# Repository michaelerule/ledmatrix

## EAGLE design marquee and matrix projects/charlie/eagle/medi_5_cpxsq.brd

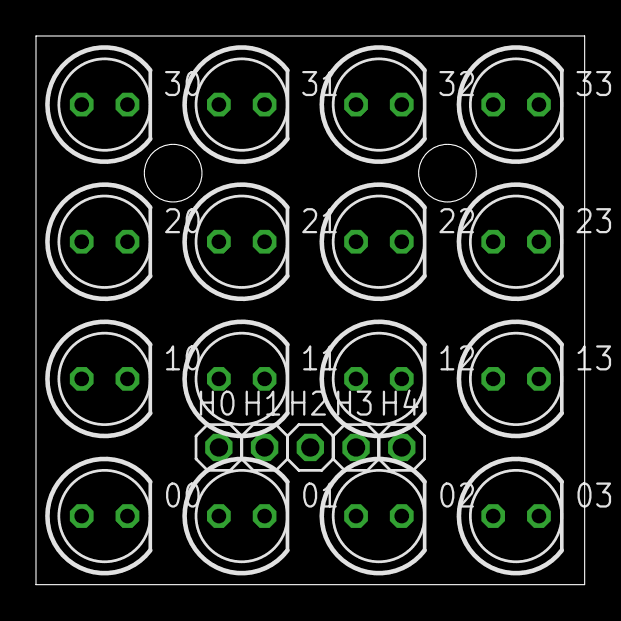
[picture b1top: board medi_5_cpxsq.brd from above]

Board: 2 copper layers, 30.5 x 30.5 mm, 21 parts (0 on the bottom side), 5 nets, no tracks yet.

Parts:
00, 01, 02, 03, 10, 11, 12, 13, 20, 21, 22, 23, 30, 31, 32, 33: LED5MM
H0, H1, H2, H3, H4: 1X01

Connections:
D: 00.A, 11.A, 22.A, 33.A, H4.1
S0: 00.K, 01.A, 02.A, 03.A, 10.K, 20.K, 30.K, H0.1
S1: 01.K, 10.A, 11.K, 12.A, 13.A, 21.K, 31.K, H1.1
S2: 02.K, 12.K, 20.A, 21.A, 22.K, 23.A, 32.K, H2.1
S3: 03.K, 13.K, 23.K, 30.A, 31.A, 32.A, 33.K, H3.1

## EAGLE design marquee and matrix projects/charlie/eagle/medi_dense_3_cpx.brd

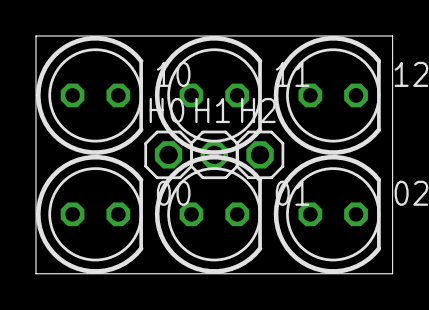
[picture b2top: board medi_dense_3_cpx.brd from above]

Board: 2 copper layers, 19.8 x 13.2 mm, 9 parts (0 on the bottom side), 3 nets, no tracks yet.

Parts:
00, 01, 02, 10, 11, 12: LED5MM
H0, H1, H2: 1X01

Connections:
D: 00.A, 02.K, 11.A, 12.K, H2.1
S0: 00.K, 01.A, 02.A, 10.K, H0.1
S1: 01.K, 10.A, 11.K, 12.A, H1.1

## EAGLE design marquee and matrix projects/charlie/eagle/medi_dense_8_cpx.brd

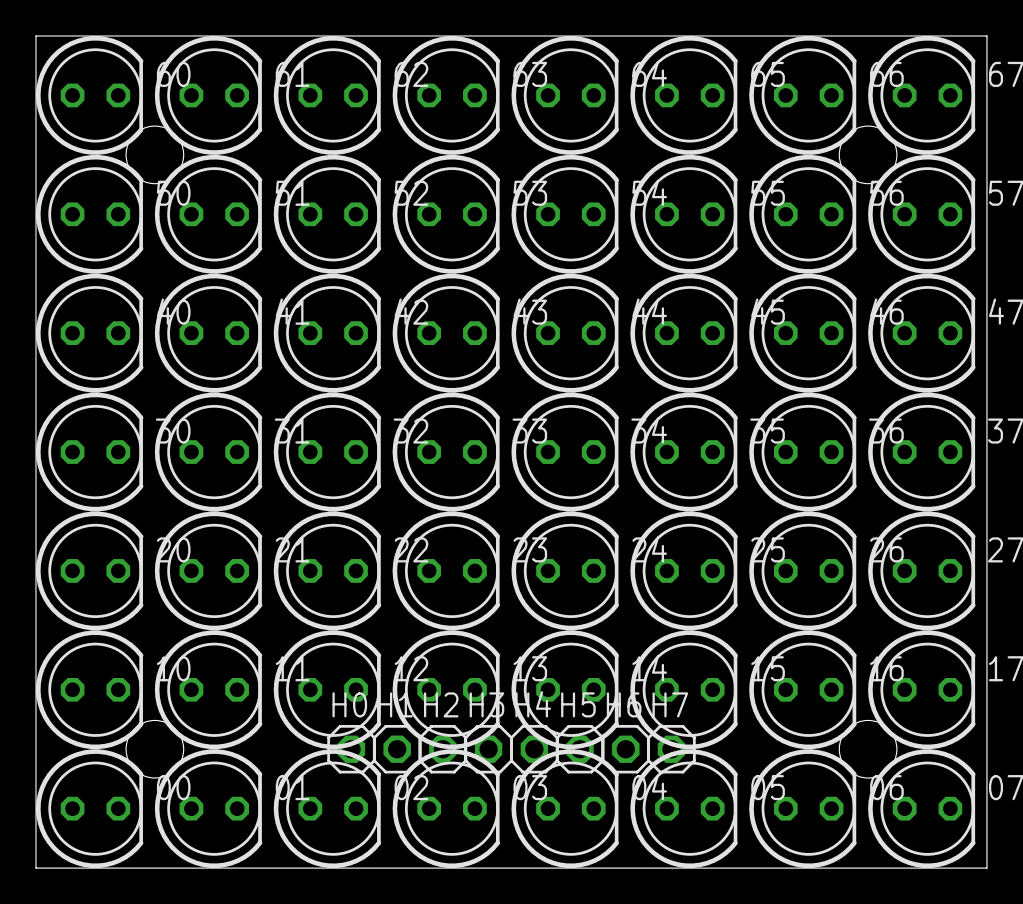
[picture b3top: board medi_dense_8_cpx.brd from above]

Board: 2 copper layers, 52.8 x 46.2 mm, 64 parts (0 on the bottom side), 8 nets, no tracks yet.

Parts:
00, 01, 02, 03, 04, 05, 06, 07, 10, 11, 12, 13, 14, 15, 16, 17, 20, 21, 22, 23, 24, 25, 26, 27, 30, 31, 32, 33, 34, 35, 36, 37, 40, 41, 42, 43, 44, 45, 46, 47, 50, 51, 52, 53, 54, 55, 56, 57, 60, 61, 62, 63, 64, 65, 66, 67: LED5MM
H0, H1, H2, H3, H4, H5, H6, H7: 1X01

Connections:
D: 00.A, 07.K, 11.A, 17.K, 22.A, 27.K, 33.A, 37.K, 44.A, 47.K, 55.A, 57.K, 66.A, 67.K, H7.1
S0: 00.K, 01.A, 02.A, 03.A, 04.A, 05.A, 06.A, 07.A, 10.K, 20.K, 30.K, 40.K, 50.K, 60.K, H0.1
S1: 01.K, 10.A, 11.K, 12.A, 13.A, 14.A, 15.A, 16.A, 17.A, 21.K, 31.K, 41.K, 51.K, 61.K, H1.1
S2: 02.K, 12.K, 20.A, 21.A, 22.K, 23.A, 24.A, 25.A, 26.A, 27.A, 32.K, 42.K, 52.K, 62.K, H2.1
S3: 03.K, 13.K, 23.K, 30.A, 31.A, 32.A, 33.K, 34.A, 35.A, 36.A, 37.A, 43.K, 53.K, 63.K, H3.1
S4: 04.K, 14.K, 24.K, 34.K, 40.A, 41.A, 42.A, 43.A, 44.K, 45.A, 46.A, 47.A, 54.K, 64.K, H4.1
S5: 05.K, 15.K, 25.K, 35.K, 45.K, 50.A, 51.A, 52.A, 53.A, 54.A, 55.K, 56.A, 57.A, 65.K, H5.1
S6: 06.K, 16.K, 26.K, 36.K, 46.K, 56.K, 60.A, 61.A, 62.A, 63.A, 64.A, 65.A, 66.K, 67.A, H6.1

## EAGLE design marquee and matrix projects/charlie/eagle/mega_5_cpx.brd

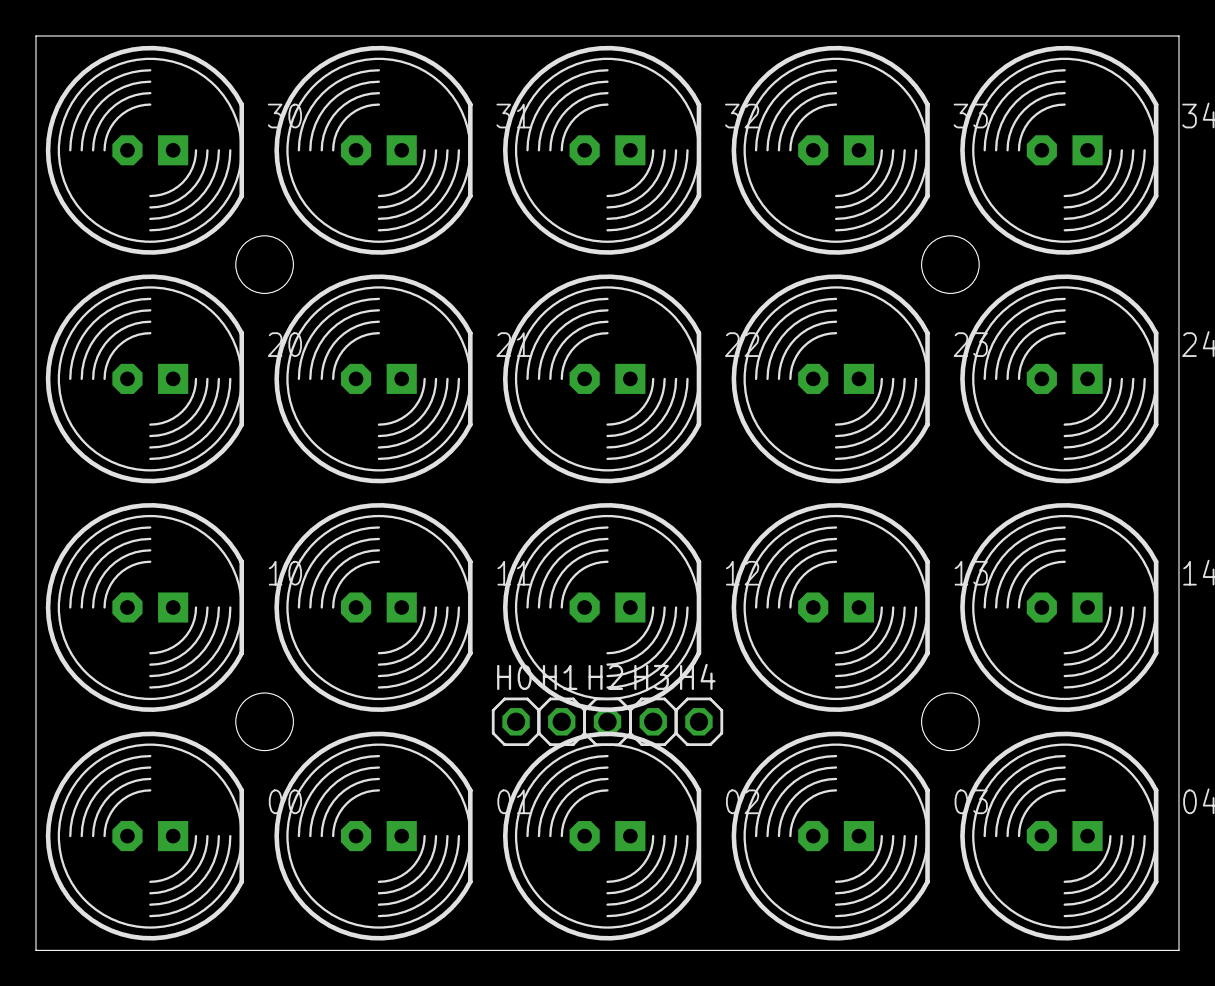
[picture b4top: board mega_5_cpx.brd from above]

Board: 2 copper layers, 63.5 x 50.8 mm, 25 parts (0 on the bottom side), 5 nets, no tracks yet.

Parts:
00, 01, 02, 03, 04, 10, 11, 12, 13, 14, 20, 21, 22, 23, 24, 30, 31, 32, 33, 34: LED10MM
H0, H1, H2, H3, H4: 1X01

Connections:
D: 00.A, 04.K, 11.A, 14.K, 22.A, 24.K, 33.A, 34.K, H4.1
S0: 00.K, 01.A, 02.A, 03.A, 04.A, 10.K, 20.K, 30.K, H0.1
S1: 01.K, 10.A, 11.K, 12.A, 13.A, 14.A, 21.K, 31.K, H1.1
S2: 02.K, 12.K, 20.A, 21.A, 22.K, 23.A, 24.A, 32.K, H2.1
S3: 03.K, 13.K, 23.K, 30.A, 31.A, 32.A, 33.K, 34.A, H3.1

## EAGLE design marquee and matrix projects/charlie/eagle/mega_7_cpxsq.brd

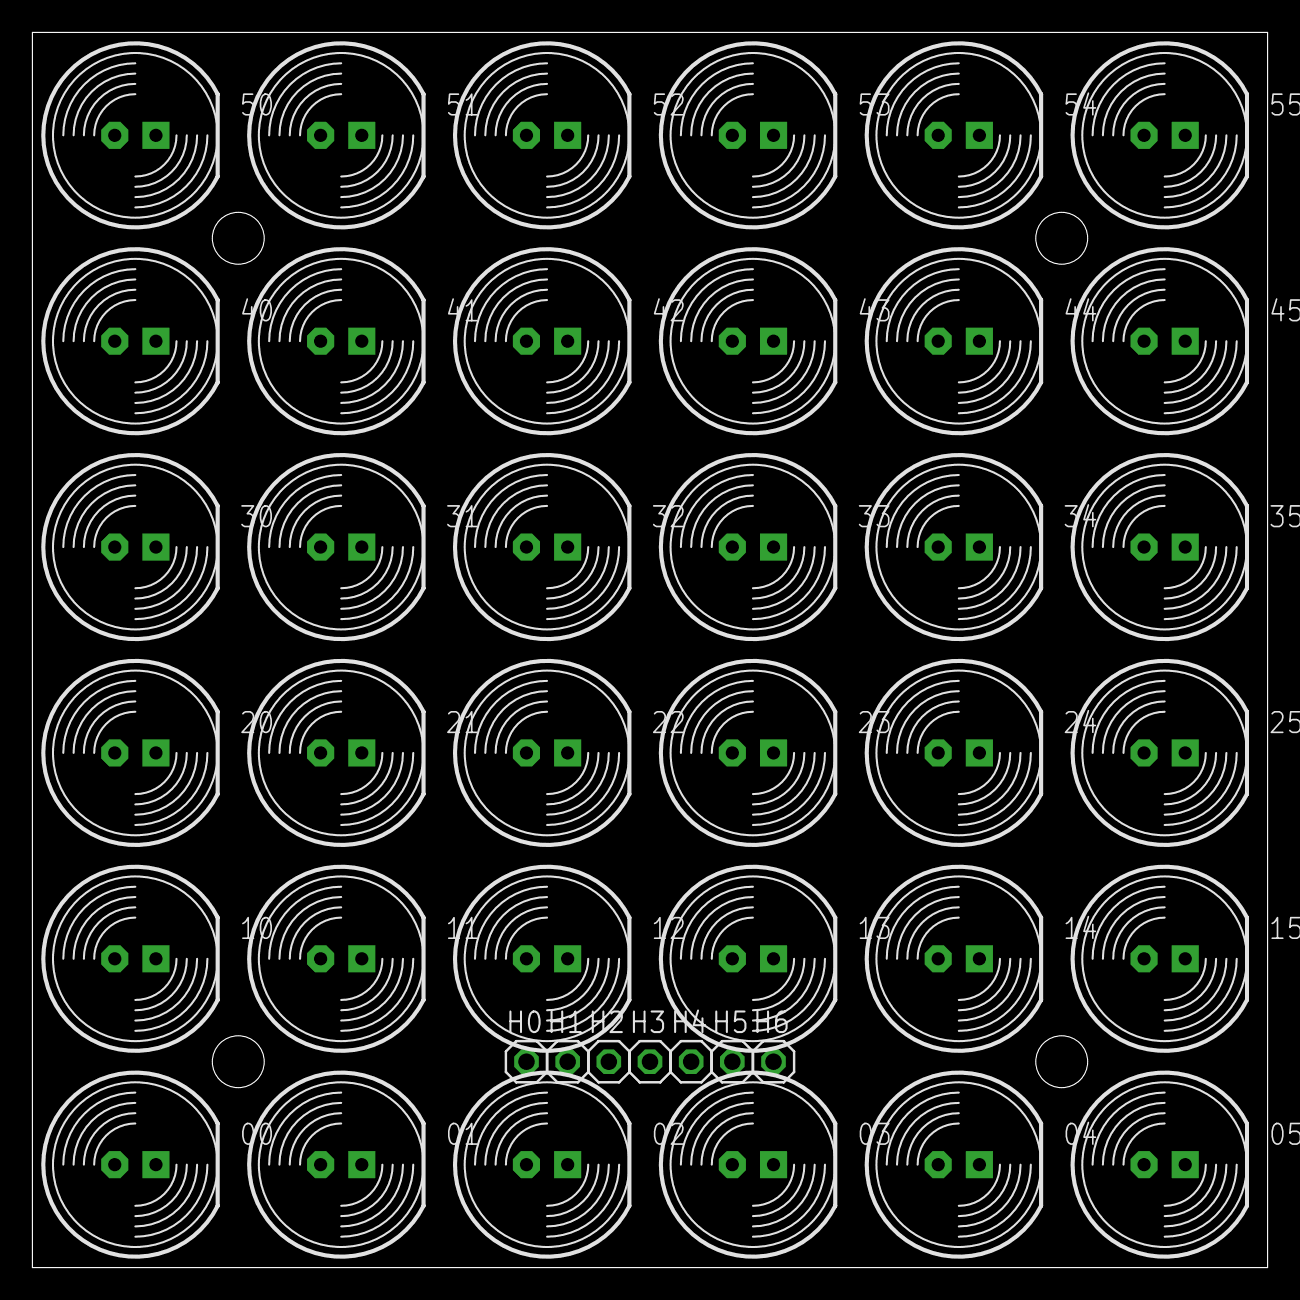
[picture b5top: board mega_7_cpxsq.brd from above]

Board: 2 copper layers, 76.2 x 76.2 mm, 43 parts (0 on the bottom side), 7 nets, no tracks yet.

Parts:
00, 01, 02, 03, 04, 05, 10, 11, 12, 13, 14, 15, 20, 21, 22, 23, 24, 25, 30, 31, 32, 33, 34, 35, 40, 41, 42, 43, 44, 45, 50, 51, 52, 53, 54, 55: LED10MM
H0, H1, H2, H3, H4, H5, H6: 1X01

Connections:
D: 00.A, 11.A, 22.A, 33.A, 44.A, 55.A, H6.1
S0: 00.K, 01.A, 02.A, 03.A, 04.A, 05.A, 10.K, 20.K, 30.K, 40.K, 50.K, H0.1
S1: 01.K, 10.A, 11.K, 12.A, 13.A, 14.A, 15.A, 21.K, 31.K, 41.K, 51.K, H1.1
S2: 02.K, 12.K, 20.A, 21.A, 22.K, 23.A, 24.A, 25.A, 32.K, 42.K, 52.K, H2.1
S3: 03.K, 13.K, 23.K, 30.A, 31.A, 32.A, 33.K, 34.A, 35.A, 43.K, 53.K, H3.1
S4: 04.K, 14.K, 24.K, 34.K, 40.A, 41.A, 42.A, 43.A, 44.K, 45.A, 54.K, H4.1
S5: 05.K, 15.K, 25.K, 35.K, 45.K, 50.A, 51.A, 52.A, 53.A, 54.A, 55.K, H5.1

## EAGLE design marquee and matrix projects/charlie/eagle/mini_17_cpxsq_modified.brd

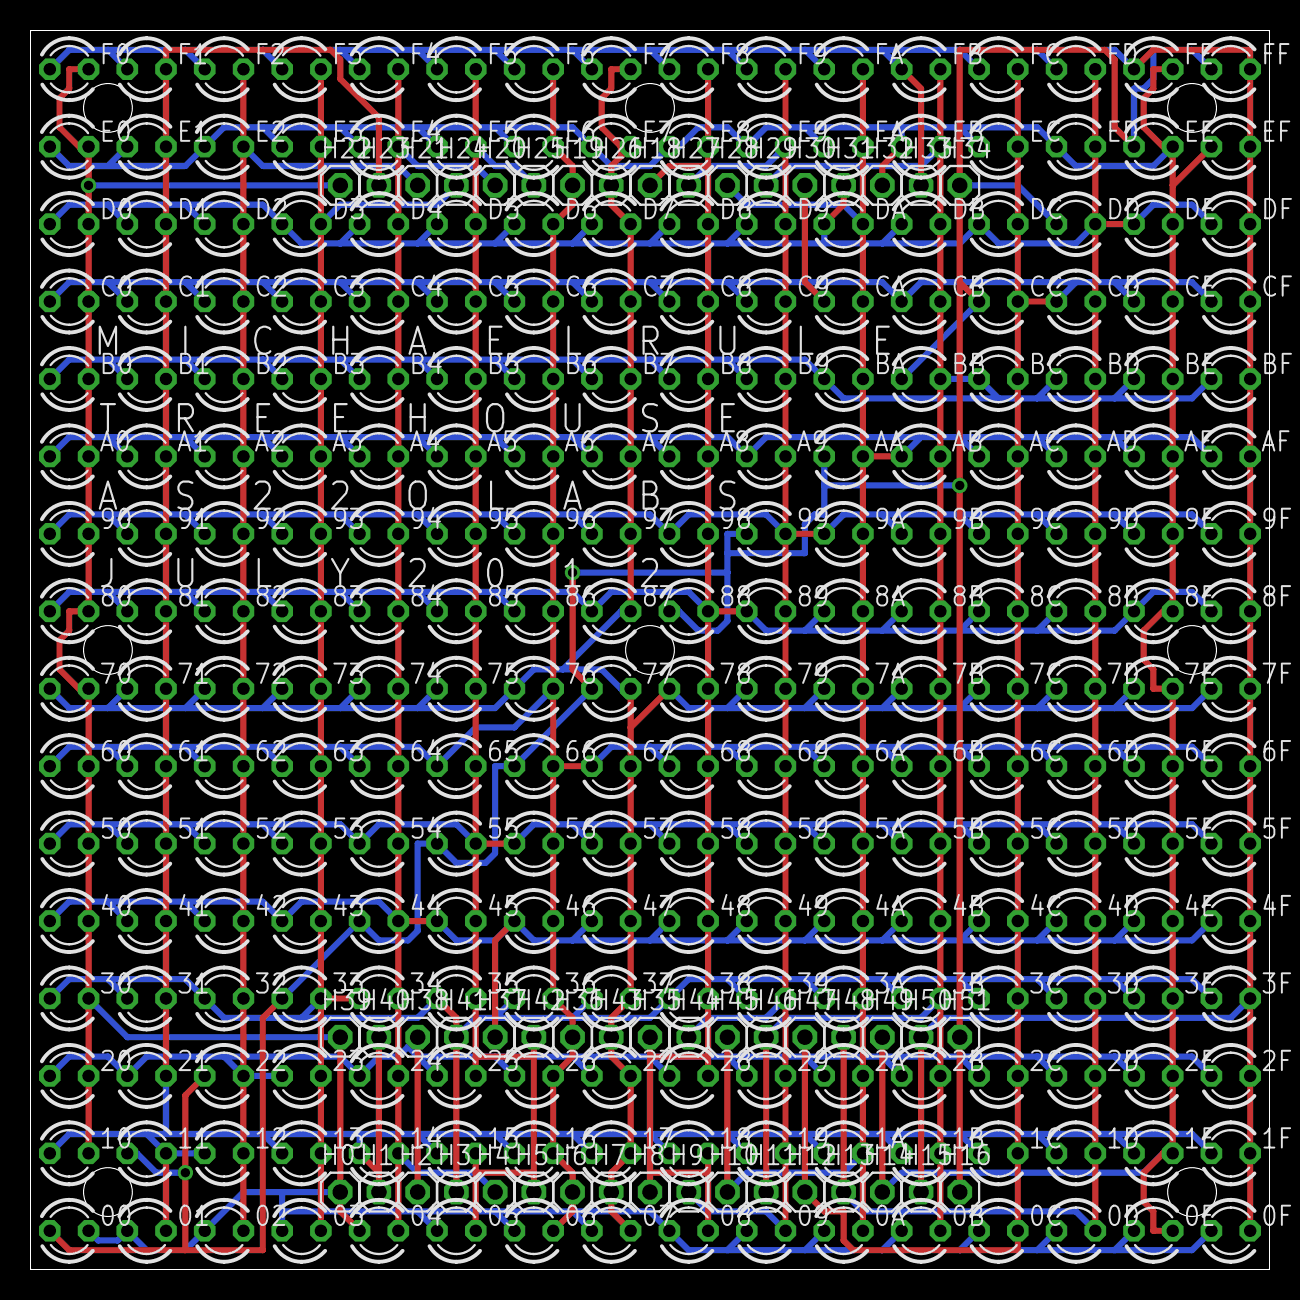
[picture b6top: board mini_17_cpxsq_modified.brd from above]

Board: 2 copper layers, 81.3 x 81.3 mm, 307 parts (0 on the bottom side), 17 nets.

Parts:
00, 0A, 0B, 0C, 0D, 0E, 0F, 01, 1A, 1B, 1C, 1D, 1E, 1F, 02, 2A, 2B, 2C, 2D, 2E, 2F, 03, 3A, 3B, 3C, 3D, 3E, 3F, 04, 4A, 4B, 4C, 4D, 4E, 4F, 05, 5A, 5B, 5C, 5D, 5E, 5F, 06, 6A, 6B, 6C, 6D, 6E, 6F, 07, 7A, 7B, 7C, 7D, 7E, 7F, 08, 8A, 8B, 8C, 8D, 8E, 8F, 09, 9A, 9B, 9C, 9D, 9E, 9F, 10, 11, 12, 13, 14, 15, 16, 17, 18, 19, 20, 21, 22, 23, 24, 25, 26, 27, 28, 29, 30, 31, 32, 33, 34, 35, 36, 37, 38, 39, 40, 41, 42, 43, 44, 45, 46, 47, 48, 49, 50, 51, 52, 53, 54, 55, 56, 57, 58, 59, 60, 61, 62, 63, 64, 65, 66, 67, 68, 69, 70, 71, 72, 73, 74, 75, 76, 77, 78, 79, 80, 81, 82, 83, 84, 85, 86, 87, 88, 89, 90, 91, 92, 93, 94, 95, 96, 97, 98, 99: LED3MM
A0, A1, A2, A3, A4, A5, A6, A7, A8, A9: LED3MM
AA: LED3MM
AB: LED3MM
AC: LED3MM
AD: LED3MM
AE: LED3MM
AF: LED3MM
B0, B1, B2, B3, B4, B5, B6, B7, B8, B9: LED3MM
BA: LED3MM
BB: LED3MM
BC: LED3MM
BD: LED3MM
BE: LED3MM
BF: LED3MM
C0, C1, C2, C3, C4, C5, C6, C7, C8, C9: LED3MM
CA: LED3MM
CB: LED3MM
CC: LED3MM
CD: LED3MM
CE: LED3MM
CF: LED3MM
D0, D1, D2, D3, D4, D5, D6, D7, D8, D9: LED3MM
DA: LED3MM
DB: LED3MM
DC: LED3MM
DD: LED3MM
DE: LED3MM
DF: LED3MM
E0, E1, E2, E3, E4, E5, E6, E7, E8, E9: LED3MM
EA: LED3MM
EB: LED3MM
EC: LED3MM
ED: LED3MM
EE: LED3MM
EF: LED3MM
F0, F1, F2, F3, F4, F5, F6, F7, F8, F9: LED3MM
FA: LED3MM
FB: LED3MM
FC: LED3MM
FD: LED3MM
FE: LED3MM
FF: LED3MM
H0, H1, H2, H3, H4, H5, H6, H7, H8, H9, H10, H11, H12, H13, H14, H15, H16, H18, H19, H20, H21, H22, H23, H24, H25, H26, H27, H28, H29, H30, H31, H32, H33, H34, H35, H36, H37, H38, H39, H40, H41, H42, H43, H44, H45, H46, H47, H48, H49, H50, H51: 1X01

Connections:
D: 00.A, 11.A, 22.A, 33.A, 44.A, 55.A, 66.A, 77.A, 88.A, 99.A, AA.A, BB.A, CC.A, DD.A, EE.A, FF.A, H16.1, H34.1, H51.1
S0: 00.K, 0A.A, 0B.A, 0C.A, 0D.A, 0E.A, 0F.A, 01.A, 02.A, 03.A, 04.A, 05.A, 06.A, 07.A, 08.A, 09.A, 10.K, 20.K, 30.K, 40.K, 50.K, 60.K, 70.K, 80.K, 90.K, A0.K, B0.K, C0.K, D0.K, E0.K, F0.K, H0.1, H22.1, H39.1
S1: 01.K, 1A.A, 1B.A, 1C.A, 1D.A, 1E.A, 1F.A, 10.A, 11.K, 12.A, 13.A, 14.A, 15.A, 16.A, 17.A, 18.A, 19.A, 21.K, 31.K, 41.K, 51.K, 61.K, 71.K, 81.K, 91.K, A1.K, B1.K, C1.K, D1.K, E1.K, F1.K, H1.1, H23.1, H40.1
S2: 02.K, 2A.A, 2B.A, 2C.A, 2D.A, 2E.A, 2F.A, 12.K, 20.A, 21.A, 22.K, 23.A, 24.A, 25.A, 26.A, 27.A, 28.A, 29.A, 32.K, 42.K, 52.K, 62.K, 72.K, 82.K, 92.K, A2.K, B2.K, C2.K, D2.K, E2.K, F2.K, H2.1, H21.1, H38.1
S3: 03.K, 3A.A, 3B.A, 3C.A, 3D.A, 3E.A, 3F.A, 13.K, 23.K, 30.A, 31.A, 32.A, 33.K, 34.A, 35.A, 36.A, 37.A, 38.A, 39.A, 43.K, 53.K, 63.K, 73.K, 83.K, 93.K, A3.K, B3.K, C3.K, D3.K, E3.K, F3.K, H3.1, H24.1, H41.1
S4: 04.K, 4A.A, 4B.A, 4C.A, 4D.A, 4E.A, 4F.A, 14.K, 24.K, 34.K, 40.A, 41.A, 42.A, 43.A, 44.K, 45.A, 46.A, 47.A, 48.A, 49.A, 54.K, 64.K, 74.K, 84.K, 94.K, A4.K, B4.K, C4.K, D4.K, E4.K, F4.K, H4.1, H20.1, H37.1
S5: 05.K, 5A.A, 5B.A, 5C.A, 5D.A, 5E.A, 5F.A, 15.K, 25.K, 35.K, 45.K, 50.A, 51.A, 52.A, 53.A, 54.A, 55.K, 56.A, 57.A, 58.A, 59.A, 65.K, 75.K, 85.K, 95.K, A5.K, B5.K, C5.K, D5.K, E5.K, F5.K, H5.1, H25.1, H42.1
S6: 06.K, 6A.A, 6B.A, 6C.A, 6D.A, 6E.A, 6F.A, 16.K, 26.K, 36.K, 46.K, 56.K, 60.A, 61.A, 62.A, 63.A, 64.A, 65.A, 66.K, 67.A, 68.A, 69.A, 76.K, 86.K, 96.K, A6.K, B6.K, C6.K, D6.K, E6.K, F6.K, H6.1, H19.1, H36.1
S7: 07.K, 7A.A, 7B.A, 7C.A, 7D.A, 7E.A, 7F.A, 17.K, 27.K, 37.K, 47.K, 57.K, 67.K, 70.A, 71.A, 72.A, 73.A, 74.A, 75.A, 76.A, 77.K, 78.A, 79.A, 87.K, 97.K, A7.K, B7.K, C7.K, D7.K, E7.K, F7.K, H7.1, H26.1, H43.1
S8: 08.K, 8A.A, 8B.A, 8C.A, 8D.A, 8E.A, 8F.A, 18.K, 28.K, 38.K, 48.K, 58.K, 68.K, 78.K, 80.A, 81.A, 82.A, 83.A, 84.A, 85.A, 86.A, 87.A, 88.K, 89.A, 98.K, A8.K, B8.K, C8.K, D8.K, E8.K, F8.K, H8.1, H18.1, H35.1
S9: 09.K, 9A.A, 9B.A, 9C.A, 9D.A, 9E.A, 9F.A, 19.K, 29.K, 39.K, 49.K, 59.K, 69.K, 79.K, 89.K, 90.A, 91.A, 92.A, 93.A, 94.A, 95.A, 96.A, 97.A, 98.A, 99.K, A9.K, B9.K, C9.K, D9.K, E9.K, F9.K, H9.1, H27.1, H44.1
S10: 0A.K, 1A.K, 2A.K, 3A.K, 4A.K, 5A.K, 6A.K, 7A.K, 8A.K, 9A.K, A0.A, A1.A, A2.A, A3.A, A4.A, A5.A, A6.A, A7.A, A8.A, A9.A, AA.K, AB.A, AC.A, AD.A, AE.A, AF.A, BA.K, CA.K, DA.K, EA.K, FA.K, H10.1, H28.1, H45.1
S11: 0B.K, 1B.K, 2B.K, 3B.K, 4B.K, 5B.K, 6B.K, 7B.K, 8B.K, 9B.K, AB.K, B0.A, B1.A, B2.A, B3.A, B4.A, B5.A, B6.A, B7.A, B8.A, B9.A, BA.A, BB.K, BC.A, BD.A, BE.A, BF.A, CB.K, DB.K, EB.K, FB.K, H11.1, H29.1, H46.1
S12: 0C.K, 1C.K, 2C.K, 3C.K, 4C.K, 5C.K, 6C.K, 7C.K, 8C.K, 9C.K, AC.K, BC.K, C0.A, C1.A, C2.A, C3.A, C4.A, C5.A, C6.A, C7.A, C8.A, C9.A, CA.A, CB.A, CC.K, CD.A, CE.A, CF.A, DC.K, EC.K, FC.K, H12.1, H30.1, H47.1
S13: 0D.K, 1D.K, 2D.K, 3D.K, 4D.K, 5D.K, 6D.K, 7D.K, 8D.K, 9D.K, AD.K, BD.K, CD.K, D0.A, D1.A, D2.A, D3.A, D4.A, D5.A, D6.A, D7.A, D8.A, D9.A, DA.A, DB.A, DC.A, DD.K, DE.A, DF.A, ED.K, FD.K, H13.1, H31.1, H48.1
S14: 0E.K, 1E.K, 2E.K, 3E.K, 4E.K, 5E.K, 6E.K, 7E.K, 8E.K, 9E.K, AE.K, BE.K, CE.K, DE.K, E0.A, E1.A, E2.A, E3.A, E4.A, E5.A, E6.A, E7.A, E8.A, E9.A, EA.A, EB.A, EC.A, ED.A, EE.K, EF.A, FE.K, H14.1, H32.1, H49.1
S15: 0F.K, 1F.K, 2F.K, 3F.K, 4F.K, 5F.K, 6F.K, 7F.K, 8F.K, 9F.K, AF.K, BF.K, CF.K, DF.K, EF.K, F0.A, F1.A, F2.A, F3.A, F4.A, F5.A, F6.A, F7.A, F8.A, F9.A, FA.A, FB.A, FC.A, FD.A, FE.A, FF.K, H15.1, H33.1, H50.1

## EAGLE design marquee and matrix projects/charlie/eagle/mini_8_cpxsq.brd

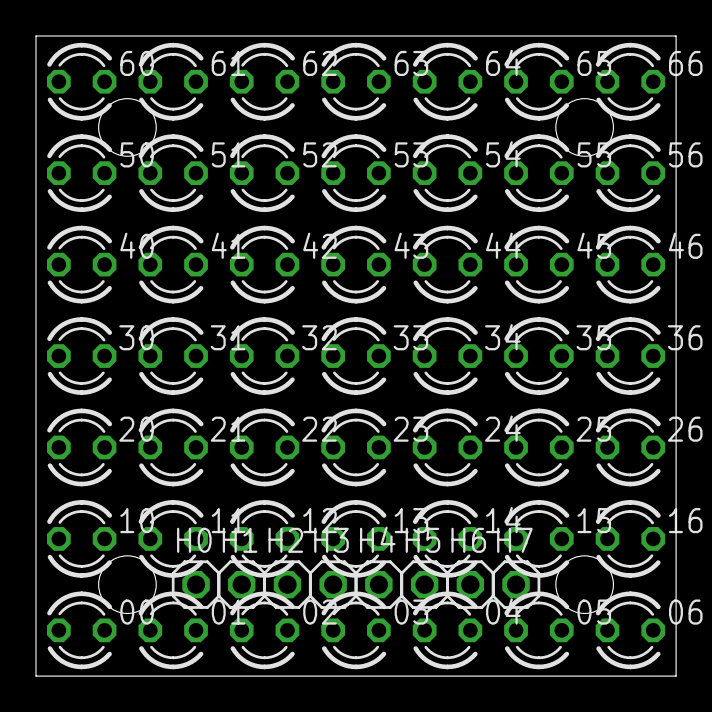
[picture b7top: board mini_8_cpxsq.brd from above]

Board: 2 copper layers, 35.6 x 35.6 mm, 57 parts (0 on the bottom side), 8 nets, no tracks yet.

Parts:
00, 01, 02, 03, 04, 05, 06, 10, 11, 12, 13, 14, 15, 16, 20, 21, 22, 23, 24, 25, 26, 30, 31, 32, 33, 34, 35, 36, 40, 41, 42, 43, 44, 45, 46, 50, 51, 52, 53, 54, 55, 56, 60, 61, 62, 63, 64, 65, 66: LED3MM
H0, H1, H2, H3, H4, H5, H6, H7: 1X01

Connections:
D: 00.A, 11.A, 22.A, 33.A, 44.A, 55.A, 66.A, H7.1
S0: 00.K, 01.A, 02.A, 03.A, 04.A, 05.A, 06.A, 10.K, 20.K, 30.K, 40.K, 50.K, 60.K, H0.1
S1: 01.K, 10.A, 11.K, 12.A, 13.A, 14.A, 15.A, 16.A, 21.K, 31.K, 41.K, 51.K, 61.K, H1.1
S2: 02.K, 12.K, 20.A, 21.A, 22.K, 23.A, 24.A, 25.A, 26.A, 32.K, 42.K, 52.K, 62.K, H2.1
S3: 03.K, 13.K, 23.K, 30.A, 31.A, 32.A, 33.K, 34.A, 35.A, 36.A, 43.K, 53.K, 63.K, H3.1
S4: 04.K, 14.K, 24.K, 34.K, 40.A, 41.A, 42.A, 43.A, 44.K, 45.A, 46.A, 54.K, 64.K, H4.1
S5: 05.K, 15.K, 25.K, 35.K, 45.K, 50.A, 51.A, 52.A, 53.A, 54.A, 55.K, 56.A, 65.K, H5.1
S6: 06.K, 16.K, 26.K, 36.K, 46.K, 56.K, 60.A, 61.A, 62.A, 63.A, 64.A, 65.A, 66.K, H6.1
